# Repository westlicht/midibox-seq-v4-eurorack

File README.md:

Hardware design files for eurorack breakout modules interfacing with custom Midibox SEQV4 build found here: https://github.com/westlicht/midibox-seq-v4

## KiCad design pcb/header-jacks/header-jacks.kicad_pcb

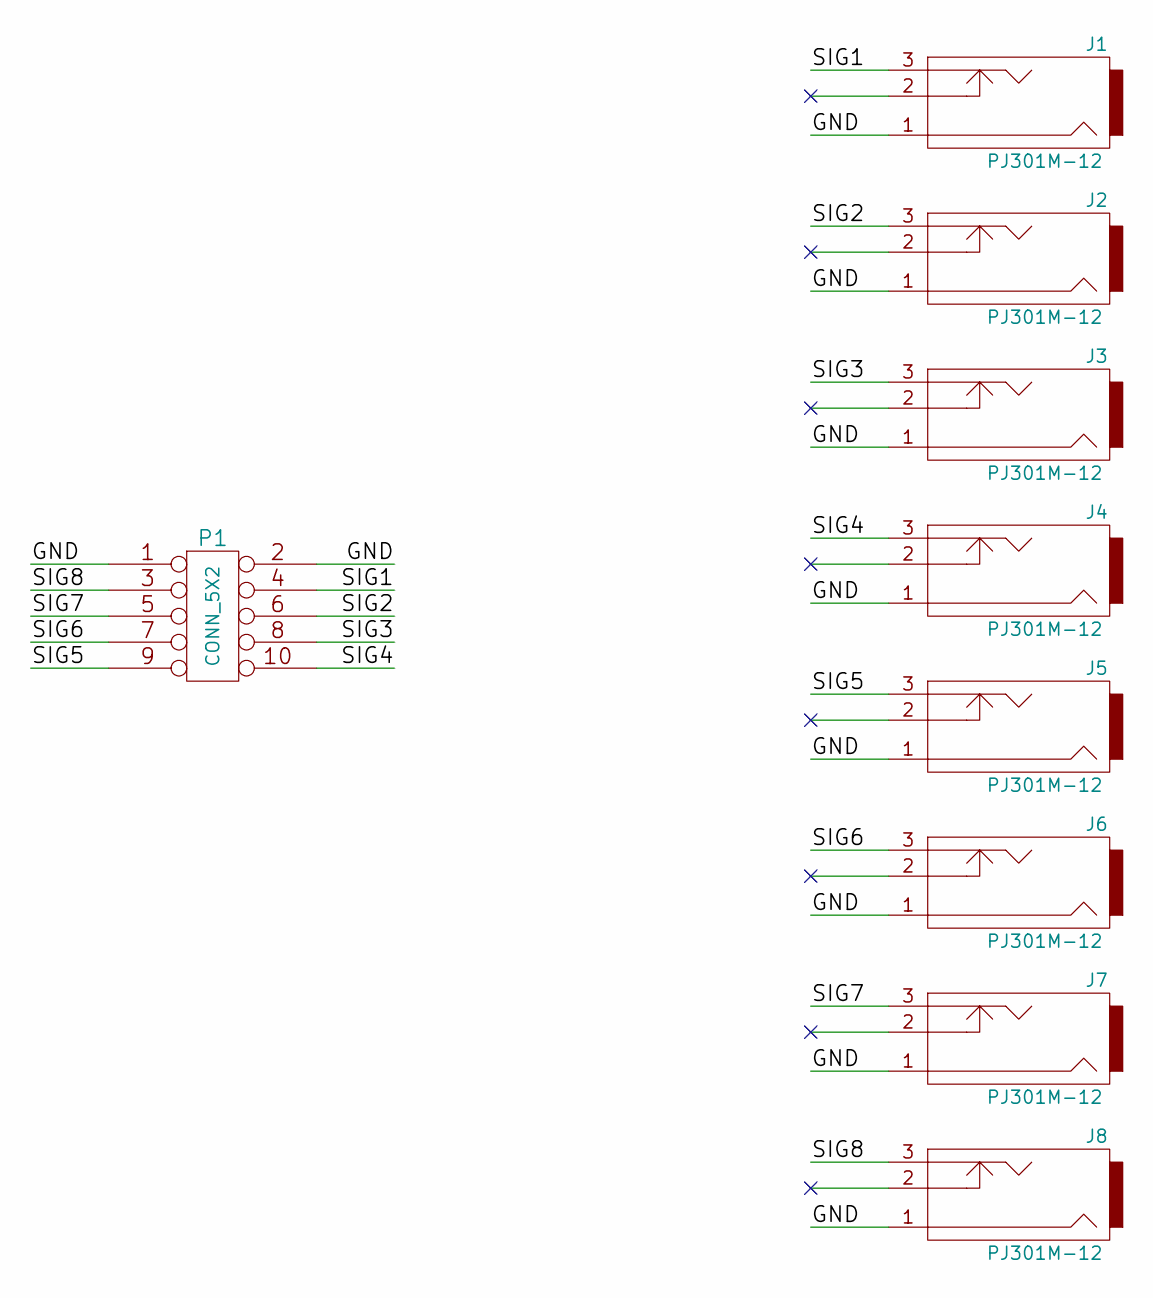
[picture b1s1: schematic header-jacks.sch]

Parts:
J1, J2, J3, J4, J5, J6, J7, J8: PJ301M-12
P1: CONN_5X2; Pin_Header_Straight_2x05_Pitch2.54mm

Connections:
/GND: J1.1, J2.1, J3.1, J4.1, J5.1, J6.1, J7.1, J8.1, P1.1, P1.2
/SIG1: J1.3, P1.4
/SIG2: J2.3, P1.6
/SIG3: J3.3, P1.8
/SIG4: J4.3, P1.10
/SIG5: J5.3, P1.9
/SIG6: J6.3, P1.7
/SIG7: J7.3, P1.5
/SIG8: J8.3, P1.3

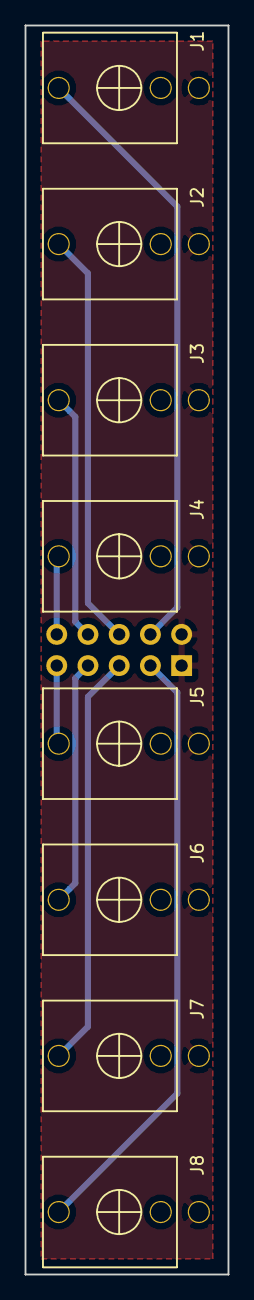
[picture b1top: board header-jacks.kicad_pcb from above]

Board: 2 copper layers, 16.5 x 101.6 mm, 9 parts (1 on the bottom side), 9 nets.

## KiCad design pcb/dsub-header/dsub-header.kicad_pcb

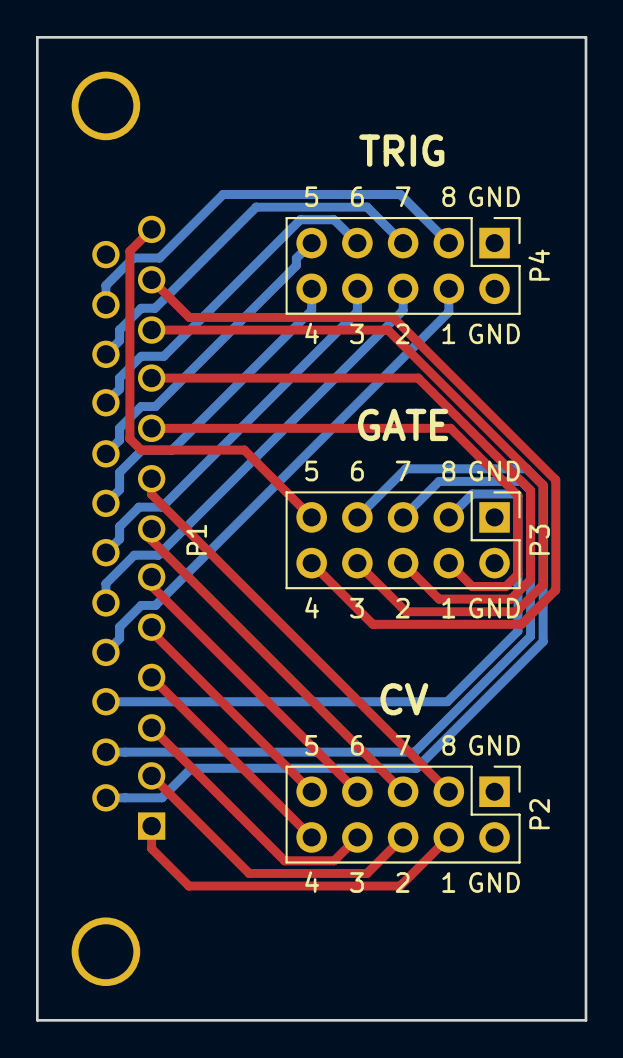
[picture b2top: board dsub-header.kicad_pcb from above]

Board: 2 copper layers, 30.5 x 54.6 mm, 4 parts (0 on the bottom side), 25 nets.

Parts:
P1: CONN_25; DB25FC
P2, P3, P4: CONN_5X2; Pin_Header_Straight_2x05_Pitch2.54mm

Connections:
/CV1: P1.1, P2.4
/CV2: P1.2, P2.6
/CV3: P1.3, P2.8
/CV4: P1.4, P2.10
/CV5: P1.5, P2.9
/CV6: P1.6, P2.7
/CV7: P1.7, P2.5
/CV8: P1.8, P2.3
/GATE1: P1.9, P3.4
/GATE2: P1.10, P3.6
/GATE3: P1.11, P3.8
/GATE4: P1.12, P3.10
/GATE5: P1.13, P3.9
/GATE6: P1.14, P3.7
/GATE7: P1.15, P3.5
/GATE8: P1.16, P3.3
/GND: P1.25, P2.1, P2.2, P3.1, P3.2, P4.1, P4.2
/TRIG1: P1.17, P4.4
/TRIG2: P1.18, P4.6
/TRIG3: P1.19, P4.8
/TRIG4: P1.20, P4.10
/TRIG5: P1.21, P4.9
/TRIG6: P1.22, P4.7
/TRIG7: P1.23, P4.5
/TRIG8: P1.24, P4.3

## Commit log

2018-09-29 initial import

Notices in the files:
pcb/dsub-header/dsub-header.kicad_pcb:
cc-by-sa Simon Kallweit 2017
